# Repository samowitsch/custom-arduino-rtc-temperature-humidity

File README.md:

# Custom arduino pcb with ssh1106, rtc ds3231, bme280, battery and eeprom.

> **Preface:** Dont exspect too much this is a private learning hobbyist project 😜

This is just a learning project of how to build/design a custom arduino pcb (Pro Micro) using a Atmega32U4.
The aim was to learn something about electronics and how to design a custom arduino pcb with [KiCad](https://kicad.org/).
In this repo you can find miscellaneous datasheets and schematics of other resources and the [KiCad](https://kicad.org/) files of this project itself. Included are also files for a simple case for cnc machining.

Dont expect to much of the source code (```custom-arduino-rtc-bme280.ino```). It looks a little bit messy. Uses a lot of libs and lots of ram. Improvements could be: the use of interrupts instead of a delay routine, get rid of the libs and write own code that uses less ram. In fact that i have not mounted rev1.1 there is no code for the eeprom. The eeprom could be used to store temperature data for a graph like display.

But these are future issues if I get around to it 😜

## Revisions

Rev | PCB                                          | Build
--- |----------------------------------------------| ---
1.0 |  | 
1.1 |  | not build yet ;o)

## Changes

**rev1.0**
* first layout

**rev1.1**
* [BUGFIX] connection of buttons was wrong
* [REMOVE] FTDI connector
* [ADD] eeprom
* [ADD] power led
* [ADD] reset button
* [ADD] regulator for v3.3 and pinheaders for v3.3 and v5.

## Experiences

* quality of ssh1106 lcd can be messy. thats annoying! complete pixel rows can be faulty after some period of time. 
* pin assignment of ssh1104 lcd can vary (VCC and SCL are swapped?). keep an eye on it!

---

> **Following now are some random notes!**

## Bootloader

* Burned Bootloader with USBasp programmer.
* Using SparkFun Pro Micro bootloader.
* Programming with Arduino IDE works with (Port depending to operating system):
  * SparkFun Pro Micro -> Atmega32U4 (5v, 16 MHz) -> /dev/ttyACM0

## Pin Mapping Arduino and 32u4

## Arduino Pin Mapping

* https://www.arduino.cc/en/Hacking/PinMapping32u4
* https://www.arduino.cc/en/Hacking/PinMapping
* https://www.arduino.cc/en/Hacking/PinMapping168

## avrdude commands

```shell script
csg@csg-deskmini-300:~$ avrdude 
Usage: avrdude [options]
Options:
  -p <partno>                Required. Specify AVR device.
  -b <baudrate>              Override RS-232 baud rate.
  -B <bitclock>              Specify JTAG/STK500v2 bit clock period (us).
  -C <config-file>           Specify location of configuration file.
  -c <programmer>            Specify programmer type.
  -D                         Disable auto erase for flash memory
  -i <delay>                 ISP Clock Delay [in microseconds]
  -P <port>                  Specify connection port.
  -F                         Override invalid signature check.
  -e                         Perform a chip erase.
  -O                         Perform RC oscillator calibration (see AVR053). 
  -U <memtype>:r|w|v:<filename>[:format]
                             Memory operation specification.
                             Multiple -U options are allowed, each request
                             is performed in the order specified.
  -n                         Do not write anything to the device.
  -V                         Do not verify.
  -u                         Disable safemode, default when running from a script.
  -s                         Silent safemode operation, will not ask you if
                             fuses should be changed back.
  -t                         Enter terminal mode.
  -E <exitspec>[,<exitspec>] List programmer exit specifications.
  -x <extended_param>        Pass <extended_param> to programmer.
  -y                         Count # erase cycles in EEPROM.
  -Y <number>                Initialize erase cycle # in EEPROM.
  -v                         Verbose output. -v -v for more.
  -q                         Quell progress output. -q -q for less.
  -l logfile                 Use logfile rather than stderr for diagnostics.
  -?                         Display this usage.

avrdude version 6.3-20171130, URL: <http://savannah.nongnu.org/projects/avrdude/>
```
 > keep option ```-u``` ```disable safemode``` in mind when using avrdude.

Read fuses:

```avrdude -c usbasp -p m32u4 -U lfuse:r:-:h -U hfuse:r:-:h -U efuse:r:-:h -U lock:r:-:h```

Write fuse example: 

```avrdude -c usbasp -p m32u4 -U lock:w:0xEF:m```

## Tools and Sketches

* https://github.com/zkemble/AVRDUDESS
* https://github.com/nickgammon/arduino_sketches - Nick Gammon
  * Atmega board detector
  * Atmega board programmer
  * Atmega fuse calculator
  * Atmega hex uploader
  * Atmega hex uploader fixed filename
  * Atmega self read signature

## Fuse online calculators

* https://www.engbedded.com/fusecalc/
* http://eleccelerator.com/fusecalc/fusecalc.php?chip=atmega32u4

## Links

* https://lastminuteengineers.com/ - cool site with detailed information about a lot of diy modules

## Notes

### Bootloader Leonardo

```shell script
csg@csg-deskmini-300:/dev$ avrdude -c usbasp -p m32u4 

avrdude: warning: cannot set sck period. please check for usbasp firmware update.
avrdude: AVR device initialized and ready to accept instructions

Reading | ################################################## | 100% 0.00s

avrdude: Device signature = 0x1e9587 (probably m32u4)

avrdude: safemode: Fuses OK (E:CB, H:D8, L:FF)

avrdude done.  Thank you.
```

### Bootloader Sparkfun Pro Micro / ATmega32U4(5V, 16 MHz)

```shell script
csg@csg-deskmini-300:/dev$ avrdude -c usbasp -p m32u4 

avrdude: warning: cannot set sck period. please check for usbasp firmware update.
avrdude: AVR device initialized and ready to accept instructions

Reading | ################################################## | 100% 0.00s

avrdude: Device signature = 0x1e9587 (probably m32u4)

avrdude: safemode: Fuses OK (E:CB, H:D8, L:FF)

avrdude done.  Thank you.
```

# serial tests

```shell script
csg@csg-deskmini-300:/dev$ dmesg | grep tty
[    0.153752] printk: console [tty0] enabled
[    2.733836] cdc_acm 1-6:1.0: ttyACM0: USB ACM device
[45121.661109] cdc_acm 1-6:1.0: ttyACM0: USB ACM device
[46330.632603] cdc_acm 1-6:1.0: ttyACM0: USB ACM device
[46436.625977] cdc_acm 1-6:1.0: ttyACM0: USB ACM device
[46652.122351] cdc_acm 1-6:1.0: ttyACM0: USB ACM device
[47043.597710] cdc_acm 1-6:1.0: ttyACM0: USB ACM device
[47101.114440] cdc_acm 1-6:1.0: ttyACM0: USB ACM device
[47151.161149] cdc_acm 1-6:1.0: ttyACM0: USB ACM device
[47153.986526] cdc_acm 1-6:1.0: ttyACM0: USB ACM device
[47252.695573] cdc_acm 1-6:1.0: ttyACM0: USB ACM device
[47255.541345] cdc_acm 1-6:1.0: ttyACM0: USB ACM device
```

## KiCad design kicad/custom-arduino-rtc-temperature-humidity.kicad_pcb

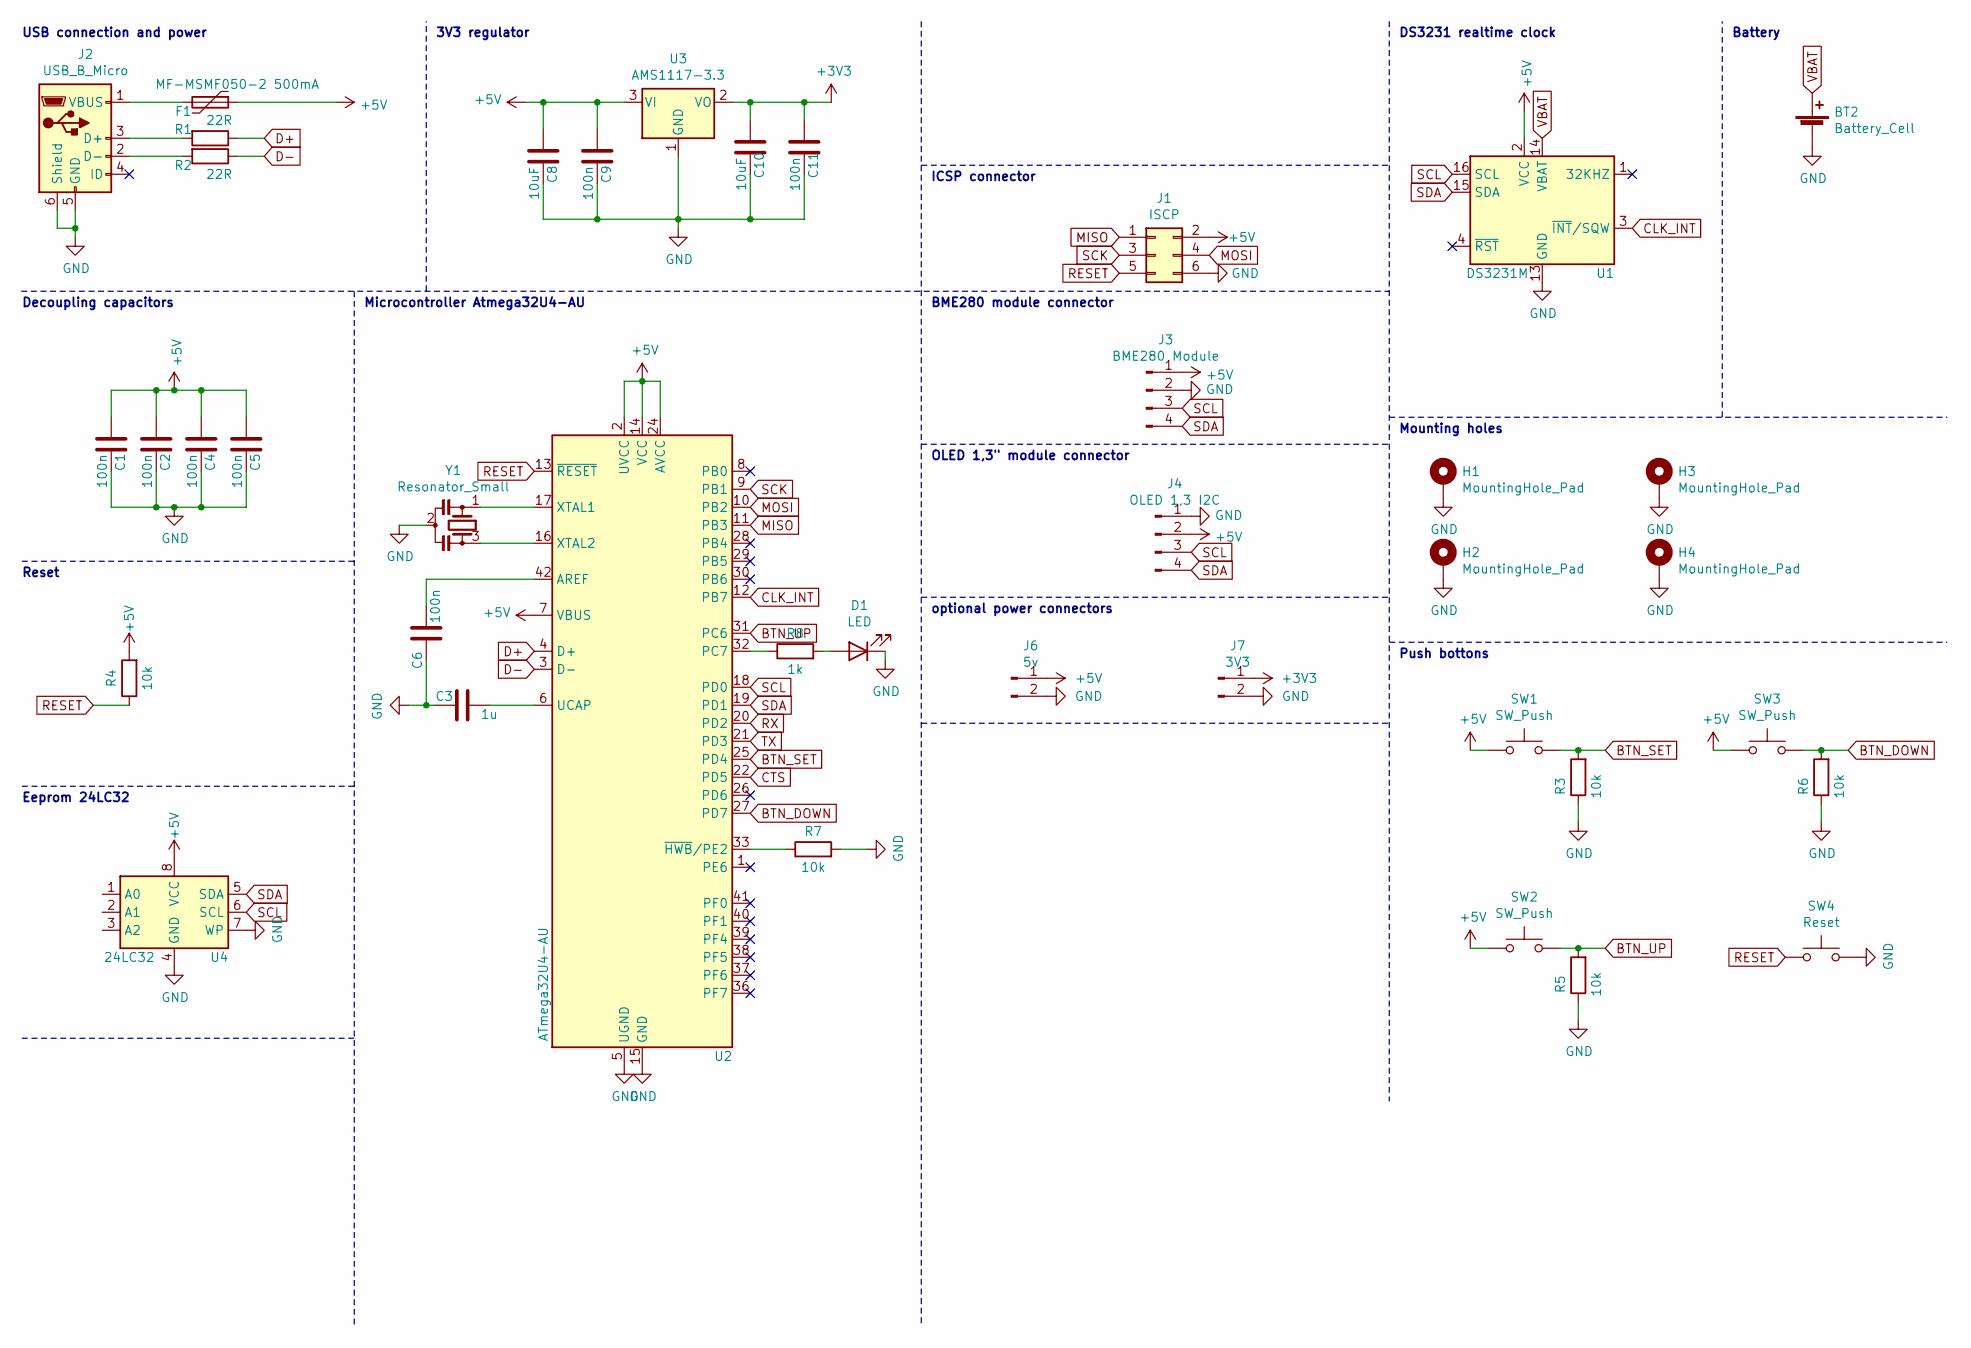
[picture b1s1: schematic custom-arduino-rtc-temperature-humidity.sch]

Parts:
BT2: Battery_Cell; CR2032-Battery-Holder
C1, C2, C4, C5, C6, C9, C11: 100n; C_0805_2012Metric_Pad1.18x1.45mm_HandSolder
C3: 1u; C_0805_2012Metric_Pad1.18x1.45mm_HandSolder
C8, C10: 10uF; C_0805_2012Metric_Pad1.18x1.45mm_HandSolder
D1: LED; LED_0805_2012Metric_Pad1.15x1.40mm_HandSolder
F1: MF-MSMF050-2 500mA; Fuse_1812_4532Metric_Pad1.30x3.40mm_HandSolder; Manufacturer # MF-MSMF050-2; Mouser Part # 652-MF-MSMF050-2
H1, H2, H3, H4: MountingHole_Pad; MountingHole_3.2mm_M3_Pad_Via
J1: ISCP; ICSP_Connector
J2: USB_B_Micro; USB_Micro-B_Amphenol_10103594-0001LF_Horizontal
J3: BME280 Module; BME280_Module
J4: OLED 1,3 I2C; SH1106_OLED_1.3_128x64_I2C
J6: 5v; PinHeader_1x02_P2.54mm_Vertical
J7: 3V3; PinHeader_1x02_P2.54mm_Vertical
R1, R2: 22R; R_0805_2012Metric_Pad1.20x1.40mm_HandSolder
R3, R4, R5, R6, R7: 10k; R_0805_2012Metric_Pad1.20x1.40mm_HandSolder
R8: 1k; R_0805_2012Metric_Pad1.20x1.40mm_HandSolder
SW1, SW2, SW3: SW_Push; SW_PUSH_6mm
SW4: Reset; SW_SPST_TL3305A
U1: DS3231M; SOIC-16W_7.5x10.3mm_P1.27mm; Manufacturer # DS3231M+; LCSC Part # C37663
U2: ATmega32U4-AU; TQFP-44_10x10mm_P0.8mm; Manufacturer # ATMEGA32U4-AU; LCSC Part # C44854
U3: AMS1117-3.3; SOT-223-3_TabPin2
U4: 24LC32; SOIC-8_3.9x4.9mm_P1.27mm
Y1: Resonator_Small; Resonator_SMD_muRata_CSTxExxV-3Pin_3.0x1.1mm_HandSoldering; Manufacturer # CSTNE16M0V51Z000R0; Mouser Part # 81-CSTNE16M0V51Z000R

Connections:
+3V3: C10.1, C11.1, J7.1, U3.2 (VO)
+5V: C1.1, C2.1, C4.1, C5.1, C8.1, C9.1, F1.1, J1.2, J3.1, J4.2, J6.1, R4.2, SW1.1, SW2.1, SW3.1, U1.2 (VCC), U2.2 (UVCC), U2.7 (VBUS), U2.14 (VCC), U2.24 (AVCC), U2.34 (VCC), U2.44 (AVCC), U3.3 (VI), U4.8 (VCC)
BTN_DOWN: R6.2, SW3.2, U2.27 (PD7)
BTN_SET: R3.2, SW1.2, U2.25 (PD4)
BTN_UP: R5.2, SW2.2, U2.31 (PC6)
CLK_INT: U1.3 (~INT~/SQW), U2.12 (PB7)
CTS: U2.22 (PD5)
D+: R1.1, U2.4 (D+)
D-: R2.1, U2.3 (D-)
GND: BT2.2 (-), C1.2, C2.2, C3.2, C4.2, C5.2, C6.1, C8.2, C9.2, C10.2, C11.2, D1.1 (K), H1.1, H2.1, H3.1, H4.1, J1.6, J2.5 (GND), J2.6 (Shield), J3.2, J4.1, J6.2, J7.2, R3.1, R5.1, R6.1, R7.2, SW4.2, U1.5 (GND), U1.6 (GND), U1.7 (GND), U1.8 (GND), U1.9 (GND), U1.10 (GND), U1.11 (GND), U1.12 (GND), U1.13 (GND), U2.5 (UGND), U2.15 (GND), U2.23 (GND), U2.35 (GND), U2.43 (GND), U3.1 (GND), U4.4 (GND), U4.7 (WP), Y1.2
MISO: J1.1, U2.11 (PB3)
MOSI: J1.4, U2.10 (PB2)
unnamed: C3.1, U2.6 (UCAP)
unnamed: C6.2, U2.42 (AREF)
unnamed: D1.2 (A), R8.2
unnamed: F1.2, J2.1 (VBUS)
unnamed: J2.2 (D-), R2.2
unnamed: J2.3 (D+), R1.2
unnamed: R7.1, U2.33 (~HWB~/PE2)
unnamed: R8.1, U2.32 (PC7)
unnamed: U2.16 (XTAL2), Y1.3
unnamed: U2.17 (XTAL1), Y1.1
RESET: J1.5, R4.1, SW4.1, U2.13 (~RESET)
RX: U2.20 (PD2)
SCK: J1.3, U2.9 (PB1)
SCL: J3.3, J4.3, U1.16 (SCL), U2.18 (PD0), U4.6 (SCL)
SDA: J3.4, J4.4, U1.15 (SDA), U2.19 (PD1), U4.5 (SDA)
TX: U2.21 (PD3)
VBAT: BT2.1 (+), U1.14 (VBAT)

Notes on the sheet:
Decoupling capacitors
USB connection and power
3V3 regulator
Reset
Microcontroller Atmega32U4-AU
ICSP connector
BME280 module connector
OLED 1,3" module connector
Mounting holes
DS3231 realtime clock
Battery
Push bottons
Eeprom 24LC32
optional power connectors

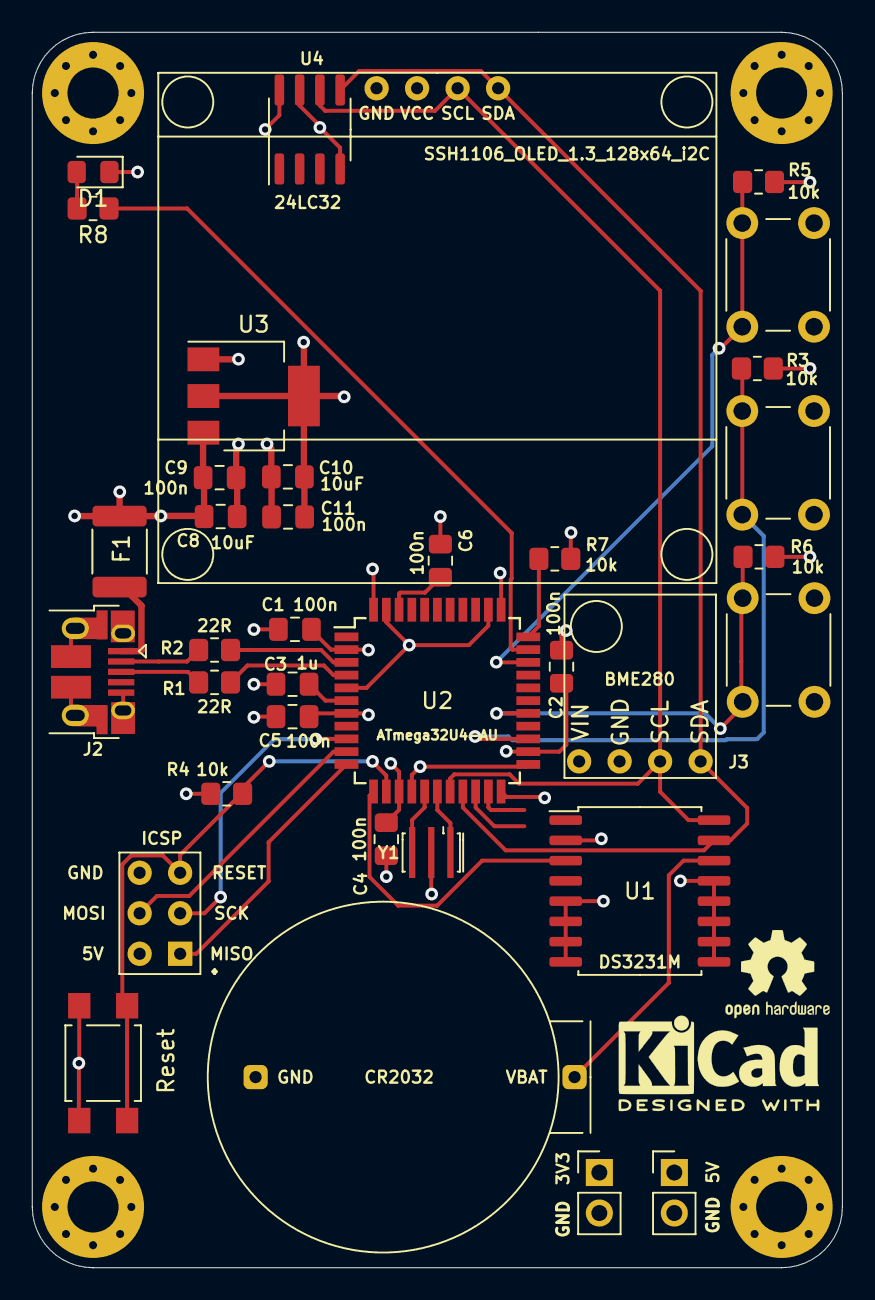
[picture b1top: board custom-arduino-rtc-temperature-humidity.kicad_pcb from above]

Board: 4 copper layers, 50.8 x 77.5 mm, 40 parts (0 on the bottom side), 26 nets.

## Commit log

2022-01-03 some readme changes
2022-01-04 fix KiCad link
2026-01-11 research more example schematics

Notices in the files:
kicad/custom-arduino-rtc-temperature-humidity.kicad_pcb:
(c) 2020 Christian Sonntag
